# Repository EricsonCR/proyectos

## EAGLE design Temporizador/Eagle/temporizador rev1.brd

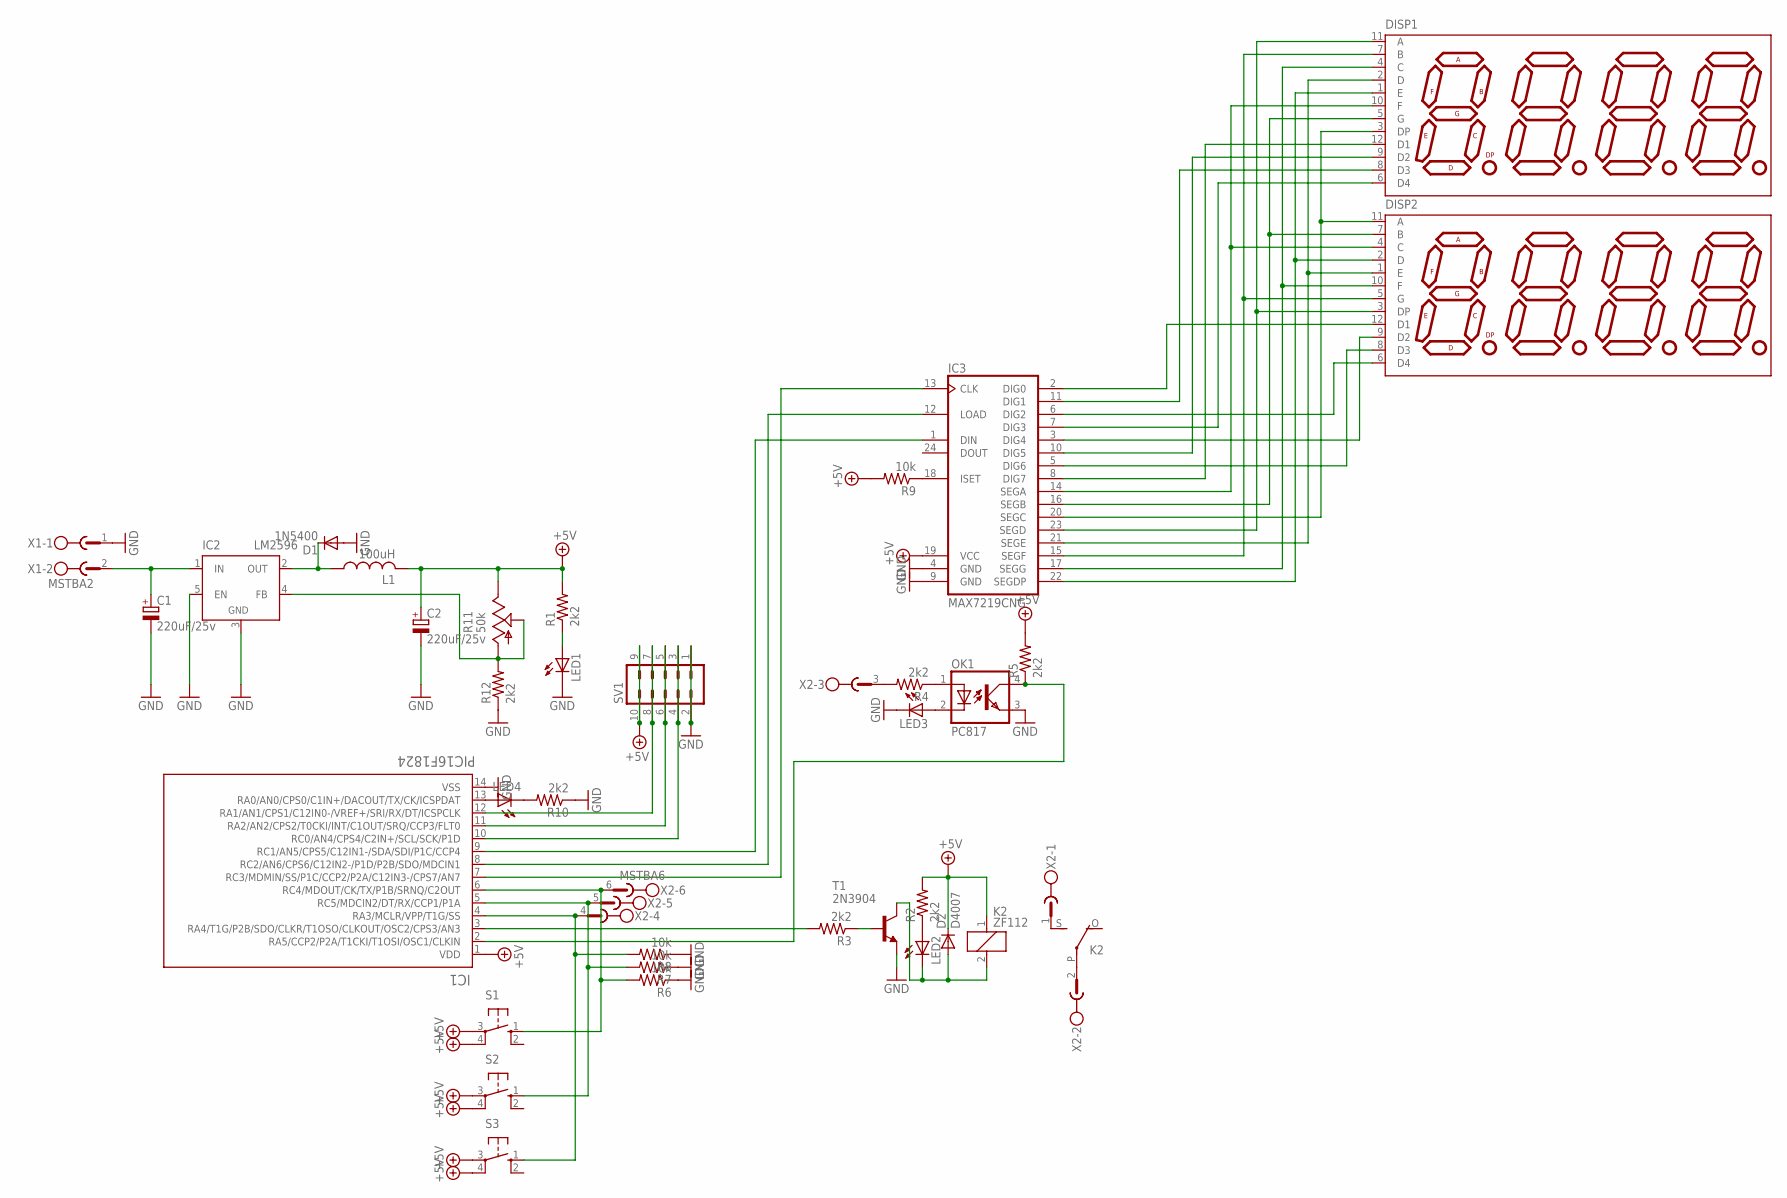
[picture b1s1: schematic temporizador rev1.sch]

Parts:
C1, C2: 220uF/25v; E3,5-10
D1: 1N5400; DO201-15
D2: D4007; DO35-10
DISP1, DISP2: DISP_7SEG_4DIG
IC1: PIC16F1824; PDIP14_300MC
IC2: LM2596; TO220-51
IC3: MAX7219CNG; DIL24-3
K2: ZF112
L1: 100uH; 6000-XXXX-RC
LED1, LED2, LED3, LED4: LED3MM
OK1: PC817; DIL04
R1, R2, R3, R4, R5, R10, R12: 2k2; 0207/10
R6, R7, R8: 10k; 0207/10
R9: 10k; R0805
R11: 50k; B25P
S1, S2, S3: 10-XX; B3F-10XX
SV1: MA05-2
T1: 2N3904; TO92-EBC
X1: MSTBA2
X2: MSTBA6

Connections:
+5V: C2.+, D2.C, IC1.1 (VDD), IC3.19 (VCC), K2.1, L1.2, R1.2, R2.2, R5.2, R9.2, R11.E, S1.3, S1.4 (P1), S2.3, S2.4 (P1), S3.3, S3.4 (P1), SV1.9, SV1.10
GND: C1.-, C2.-, D1.A, IC1.14 (VSS), IC2.3 (GND), IC2.5 (EN), IC3.4 (GND), IC3.9 (GND), LED1.K (C), LED3.K (C), OK1.3 (EMIT), R6.1, R7.1, R8.1, R10.1, R12.1, SV1.1, SV1.2, T1.E, X1.1
unnamed: LED1.A, R1.1
unnamed: C1.+, IC2.1 (IN), X1.2
unnamed: D1.C, IC2.2 (OUT), L1.1
unnamed: DISP1.3 (DP), DISP2.11 (A), IC3.20 (SEGC)
unnamed: DISP1.2 (D), DISP2.1 (E), IC3.21 (SEGE)
unnamed: DISP1.1 (E), DISP2.2 (D), IC3.22 (SEGDP)
unnamed: DISP1.4 (C), DISP2.10 (F), IC3.17 (SEGG)
unnamed: IC3.18 (ISET), R9.1
unnamed: DISP1.5 (G), DISP2.7 (B), IC3.16 (SEGB)
unnamed: DISP1.11 (A), DISP2.3 (DP), IC3.23 (SEGD)
unnamed: DISP1.7 (B), DISP2.5 (G), IC3.15 (SEGF)
unnamed: LED2.A, R2.1
unnamed: R3.1, T1.B
unnamed: D2.A, K2.2, LED2.K (C), T1.C
unnamed: OK1.1 (A), R4.1
unnamed: LED3.A, OK1.2 (C)
unnamed: IC1.6 (RC4/MDOUT/CK/TX/P1B/SRNQ/C2OUT), R6.2, S1.1 (S), X2.6
unnamed: IC1.3 (RA4/T1G/P2B/SDO/CLKR/T1OSO/CLKOUT/OSC2/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), R3.2
unnamed: IC1.2 (RA5/CCP2/P2A/T1CKI/T1OSI/OSC1/CLKIN), OK1.4 (COL), R5.1
unnamed: IC1.5 (RC5/MDCIN2/DT/RX/CCP1/P1A), R7.2, S2.1 (S), X2.5
unnamed: IC1.4 (RA3/MCLR/VPP/T1G/SS), R8.2, S3.1 (S), X2.4
unnamed: DISP1.10 (F), DISP2.4 (C), IC3.14 (SEGA)
unnamed: IC1.8 (RC2/AN6/CPS6/C12IN2-/P1D/P2B/SDO/MDCIN1), IC3.12 (LOAD)
unnamed: IC1.9 (RC1/AN5/CPS5/C12IN1-/SDA/SDI/P1C/CCP4), IC3.1 (DIN)
unnamed: IC1.7 (RC3/MDMIN/SS/P1C/CCP2/P2A/C12IN3-/CPS7/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), IC3.13 (CLK)
unnamed: K2.S, X2.1
unnamed: K2.P, X2.2
unnamed: R4.2, X2.3
unnamed: IC1.13 (RA0/AN0/CPS0/C1IN+/DACOUT/TX/CK/ICSPDAT), LED4.A
unnamed: LED4.K (C), R10.2
unnamed: IC1.12 (RA1/AN1/CPS1/C12IN0-/VREF+/SRI/RX/DT/IC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), SV1.7, SV1.8
unnamed: IC1.11 (RA2/AN2/CPS2/T0CKI/INT/C1OUT/SRQ/CCP3/F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), SV1.5, SV1.6
unnamed: IC1.10 (RC0/AN4/CPS4/C2IN+/SCL/SCK/P1D), SV1.3, SV1.4
unnamed: DISP1.6 (D4), IC3.7 (DIG3)
unnamed: DISP1.12 (D1), IC3.8 (DIG7)
unnamed: DISP1.9 (D2), IC3.10 (DIG5)
unnamed: DISP1.8 (D3), IC3.11 (DIG1)
unnamed: DISP2.6 (D4), IC3.6 (DIG2)
unnamed: DISP2.8 (D3), IC3.5 (DIG6)
unnamed: DISP2.9 (D2), IC3.3 (DIG4)
unnamed: DISP2.12 (D1), IC3.2 (DIG0)
unnamed: IC2.4 (FB), R11.A, R11.S, R12.2

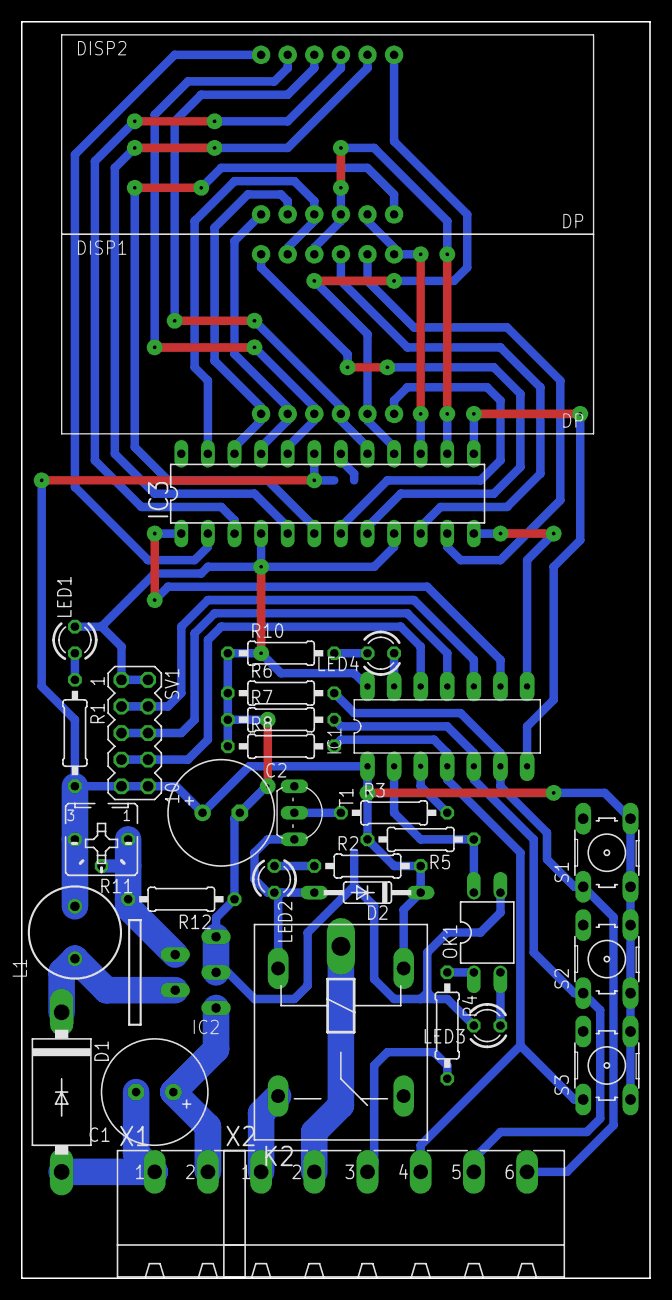
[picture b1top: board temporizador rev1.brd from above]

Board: 2 copper layers, 60.0 x 120.0 mm, 35 parts (1 on the bottom side), 44 nets.

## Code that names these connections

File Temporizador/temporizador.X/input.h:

/* 
 * File:   input.h
 * Author: Ericson
 *
 * Created on 6 de abril de 2020, 07:24 PM
 */

#ifndef INPUT_H
#define	INPUT_H

#define opto            PORTAbits.RA5
#define opto_tris       TRISAbits.TRISA5
#define pulsador_subir  PORTAbits.RA3
#define subir_tris      TRISAbits.TRISA3
#define pulsador_bajar  PORTCbits.RC5
#define bajar_tris      TRISCbits.TRISC5
#define pulsador_ok     PORTCbits.RC4
#define ok_tris         TRISCbits.TRISC4

void input_config(void) {
    opto_tris = 1;
    subir_tris = 1;
    bajar_tris = 1;
    ok_tris = 1;
}

unsigned int input_pulsador_subir(void) {
    static int contador = 0;
    if (pulsador_subir) {
        if (++contador > 10000) {
            contador = 0;
            return 1;
        }
    } else {
        contador = 0;
        return 0;
    }
    return 0;
}

unsigned int input_pulsador_bajar(void) {
    static int contador = 0;
    if (pulsador_bajar) {
        if (++contador > 10000) {
            contador = 0;
            return 1;
        }
    } else {
        contador = 0;
        return 0;
    }
    return 0;
}

unsigned int input_pulsador_ok(void) {
    static int contador = 0;
    if (pulsador_ok) {
        if (++contador > 10000) {
            contador = 0;
            return 1;
        }
    } else {
        contador = 0;
        return 0;
    }
    return 0;
}
#endif	/* INPUT_H */
